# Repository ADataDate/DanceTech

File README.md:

# Dance and Cheer Tech

Creative computing kits for dancers and cheerleaders

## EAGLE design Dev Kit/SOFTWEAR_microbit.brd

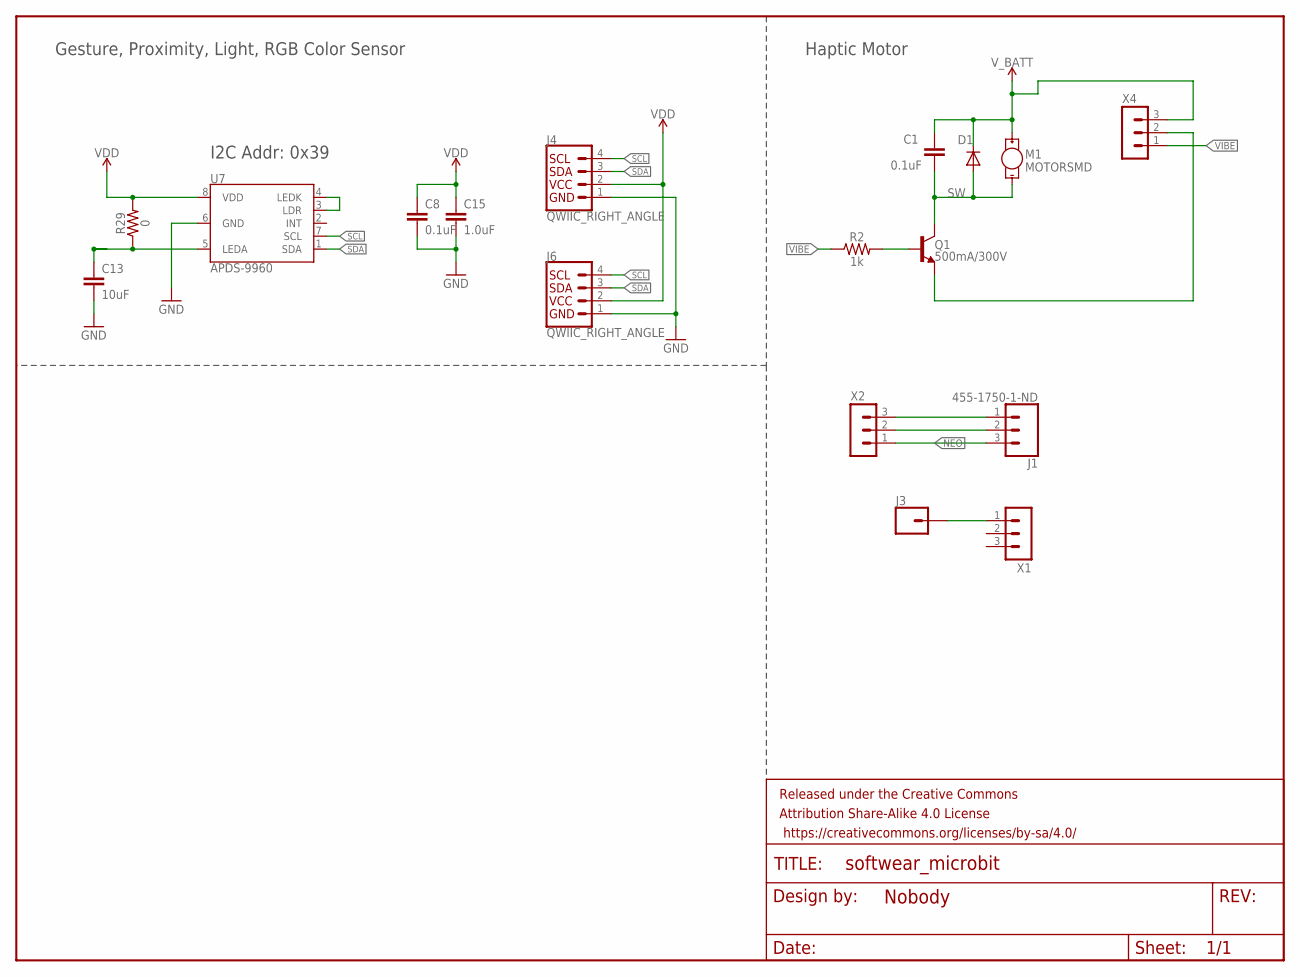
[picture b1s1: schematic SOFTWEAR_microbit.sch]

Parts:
C1, C8: 0.1uF; 0603
C13: 10uF; 0805
C15: 1.0uF; 0603
D1: DIODESOD; SOD-323
FRAME2: FRAME-LETTERNO_PACKAGE; DUMMY
J1: 455-1750-1-ND; 1X03
J3: CONN_01SPRING-CONN; SPRING-CONNECTOR
J4, J6: QWIIC_RIGHT_ANGLE; JST04_1MM_RA
M1: MOTORSMD; VIBE-MOTOR-10MM-SMD
Q1: 500mA/300V; SOT23-3
R2: 1k; 0603
R29: 0; 0603
U7: APDS-9960
X1, X2, X4: SM03B-SRSS-TB

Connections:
GND: C8.2, C13.2, C15.2, J4.1, J6.1, U7.6 (GND)
LEDA: C13.1, R29.1, U7.5 (LEDA)
unnamed: Q1.1 (B), R2.2
unnamed: J1.2, X2.2
unnamed: U7.3 (LDR), U7.4 (LEDK)
unnamed: J3.P$2, X1.1
unnamed: J1.1, X2.3
unnamed: Q1.2 (E), X4.2
NEO: J1.3, X2.1
SCL: J4.4, J6.4, U7.7 (SCL)
SDA: J4.3, J6.3, U7.1 (SDA)
SW: C1.2, D1.2 (A), M1.P$2 (-), Q1.3 (C)
VDD: C8.1, C15.1, J4.2, J6.2, R29.2, U7.8 (VDD)
VIBE: R2.1, X4.1
V_BATT: C1.1, D1.1 (C), M1.P$1 (+), X4.3

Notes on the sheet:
Haptic Motor
I2C Addr: 0x39
Gesture, Proximity, Light, RGB Color Sensor

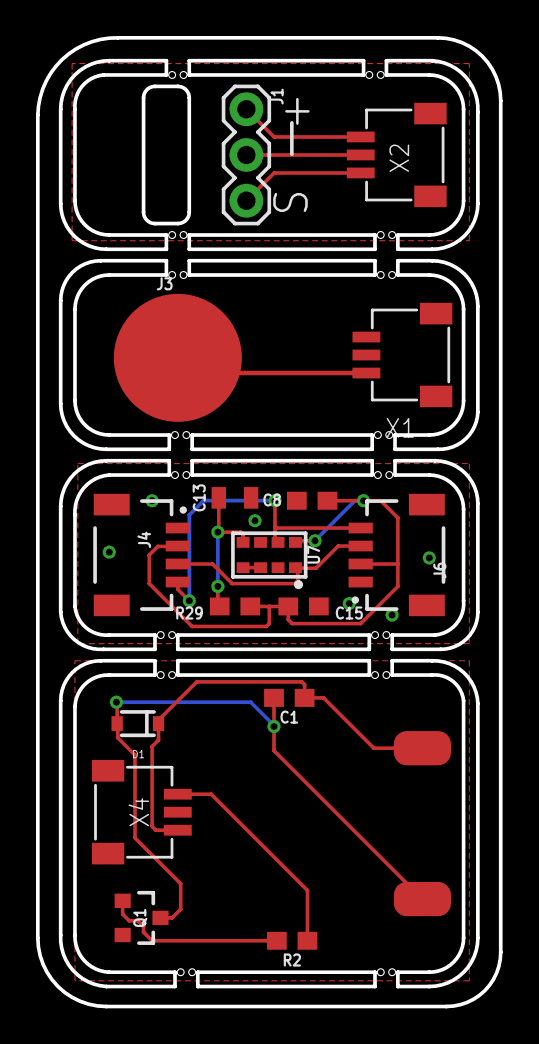
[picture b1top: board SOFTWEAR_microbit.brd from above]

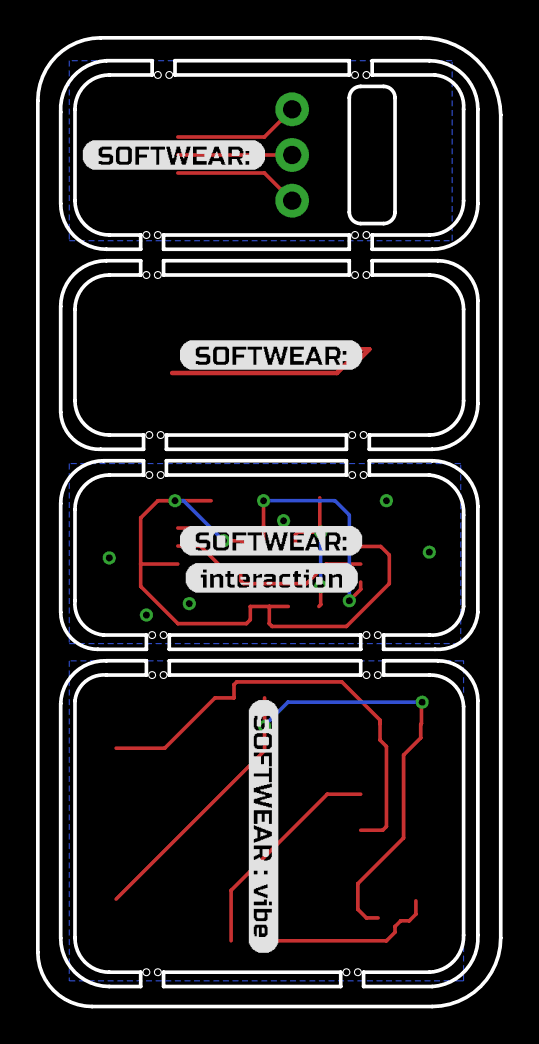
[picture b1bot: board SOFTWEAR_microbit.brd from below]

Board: 2 copper layers, 25.7 x 53.8 mm, 23 parts (5 on the bottom side), 15 nets.

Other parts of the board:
U$1, U$4, U$6: SOFTWEAR#3
U$2: INTERACTION1
U$5: SOFTWEAR_#_VIBE6

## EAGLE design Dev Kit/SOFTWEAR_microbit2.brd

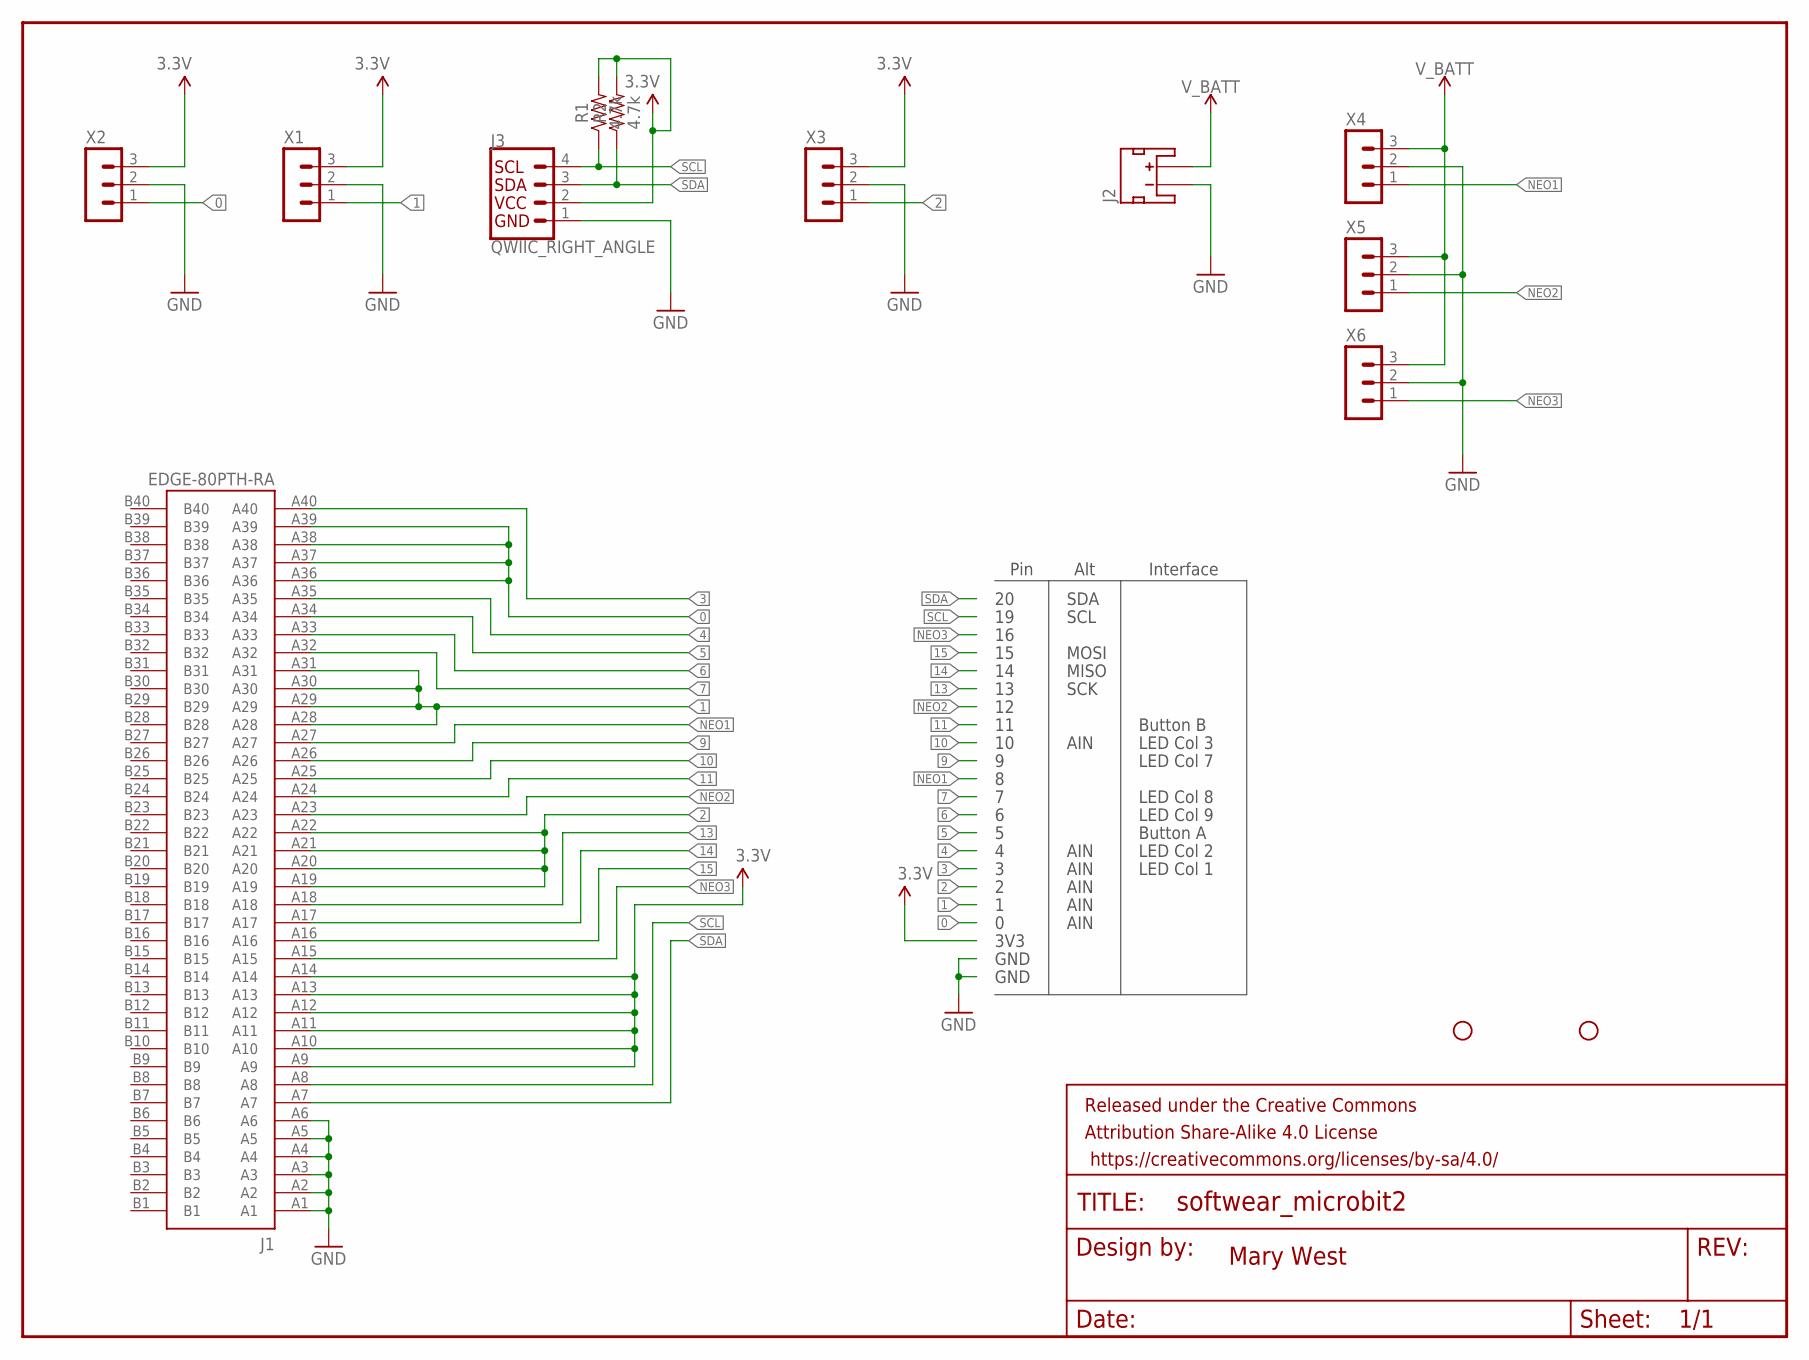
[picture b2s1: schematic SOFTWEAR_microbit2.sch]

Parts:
FRAME2: FRAME-LETTERNO_PACKAGE; DUMMY
H1, H2: STAND-OFF
J1: EDGE-80PTH-RA; VEC-127-080-R
J2: JST_2MM_MALE; JST-2-SMD
J3: QWIIC_RIGHT_ANGLE; JST04_1MM_RA
R1, R2: 4.7k; 0603
X1, X2, X3, X4, X5, X6: SM03B-SRSS-TB

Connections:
0: J1.A36, J1.A37, J1.A38, J1.A39, X2.1
1: J1.A28, J1.A29, J1.A30, J1.A31, X1.1
2: J1.A19, J1.A20, J1.A21, J1.A22, X3.1
3: J1.A40
3.3V: J1.A9, J1.A10, J1.A11, J1.A12, J1.A13, J1.A14, J3.2, R1.2, R2.2, X1.3, X2.3, X3.3
4: J1.A35
5: J1.A34
6: J1.A33
7: J1.A32
9: J1.A26
10: J1.A25
11: J1.A24
13: J1.A18
14: J1.A17
15: J1.A16
GND: J1.A1, J1.A2, J1.A3, J1.A4, J1.A5, J1.A6, J2.1 (-), J3.1, X1.2, X2.2, X3.2, X4.2, X5.2, X6.2
NEO1: J1.A27, X4.1
NEO2: J1.A23, X5.1
NEO3: J1.A15, X6.1
SCL: J1.A8, J3.4, R1.1
SDA: J1.A7, J3.3, R2.1
V_BATT: J2.2 (+), X4.3, X5.3, X6.3

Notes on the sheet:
GND
3V3
SCL
SDA
SCK
MISO
MOSI
AIN
Button B
LED Col 3
LED Col 7
LED Col 8
LED Col 9
LED Col 2
Button A
LED Col 1
Pin
Alt
Interface
Mary West

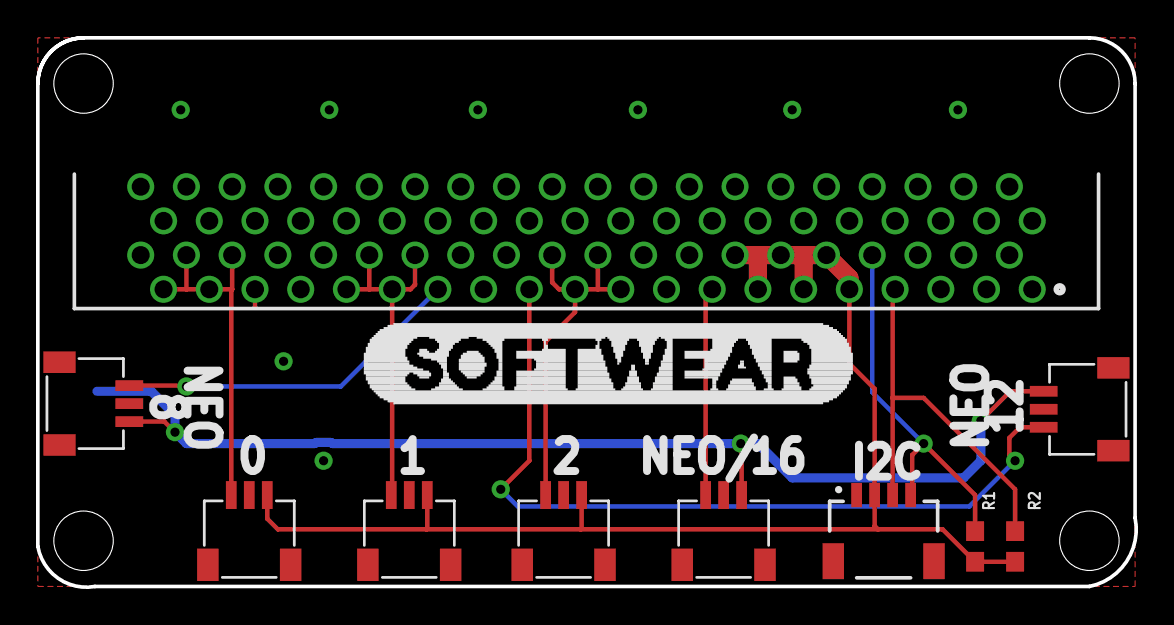
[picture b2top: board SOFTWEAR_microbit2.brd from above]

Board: 2 copper layers, 61.0 x 30.5 mm, 17 parts (1 on the bottom side), 11 nets.

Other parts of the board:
H3, H4: STAND-OFF
U$1: SOFTWEAR0

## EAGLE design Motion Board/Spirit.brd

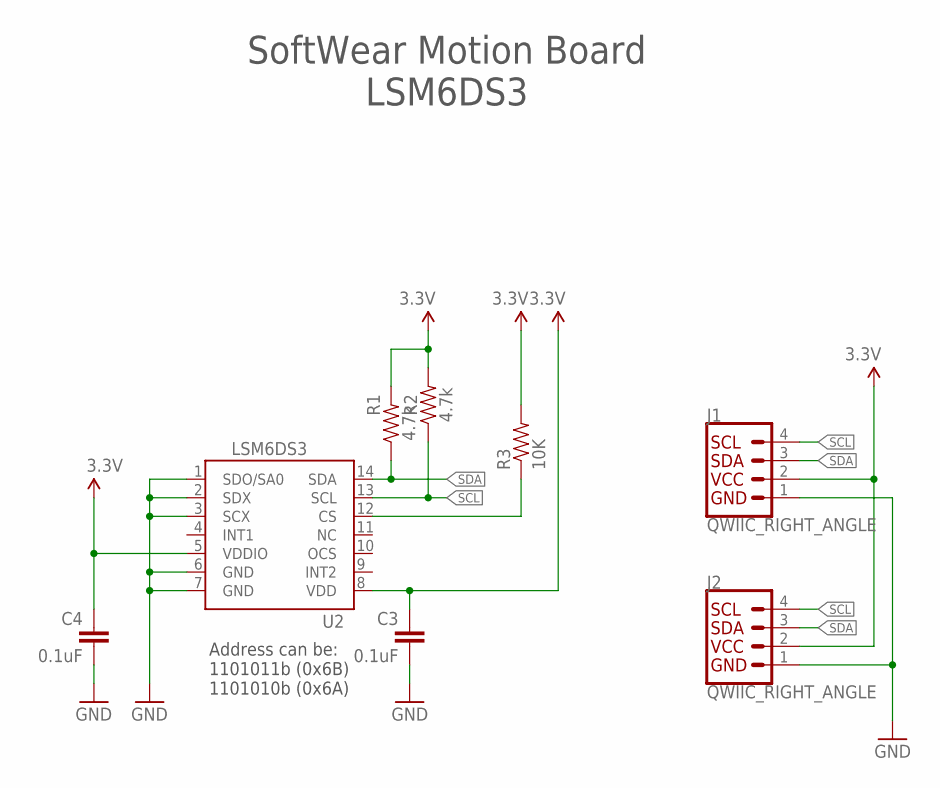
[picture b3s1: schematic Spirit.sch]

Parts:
C3, C4: 0.1uF; 0603-CAP
J1, J2: QWIIC_RIGHT_ANGLE; JST04_1MM_RA
R1, R2: 4.7k; 0603
R3: 10K; 0603-RES
U2: LSM6DS3; LGA14L_DOT_INDICATOR

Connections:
3.3V: C3.1, C4.1, J1.2, J2.2, R1.2, R2.2, R3.2, U2.5 (VDDIO), U2.8 (VDD)
CS: R3.1, U2.12 (CS)
GND: C3.2, C4.2, J1.1, J2.1, U2.1 (SDO/SA0), U2.2 (SDX), U2.3 (SCX), U2.6 (GND), U2.7 (GND)
SCL: J1.4, J2.4, R2.1, U2.13 (SCL)
SDA: J1.3, J2.3, R1.1, U2.14 (SDA)

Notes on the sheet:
SoftWear Motion Board LSM6DS3
Address can be: 1101011b (0x6B) 1101010b (0x6A)

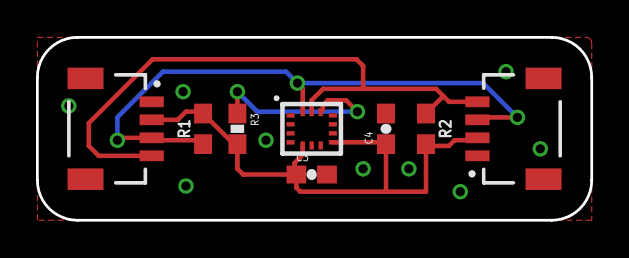
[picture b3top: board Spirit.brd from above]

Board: 2 copper layers, 30.8 x 10.2 mm, 8 parts (0 on the bottom side), 5 nets.

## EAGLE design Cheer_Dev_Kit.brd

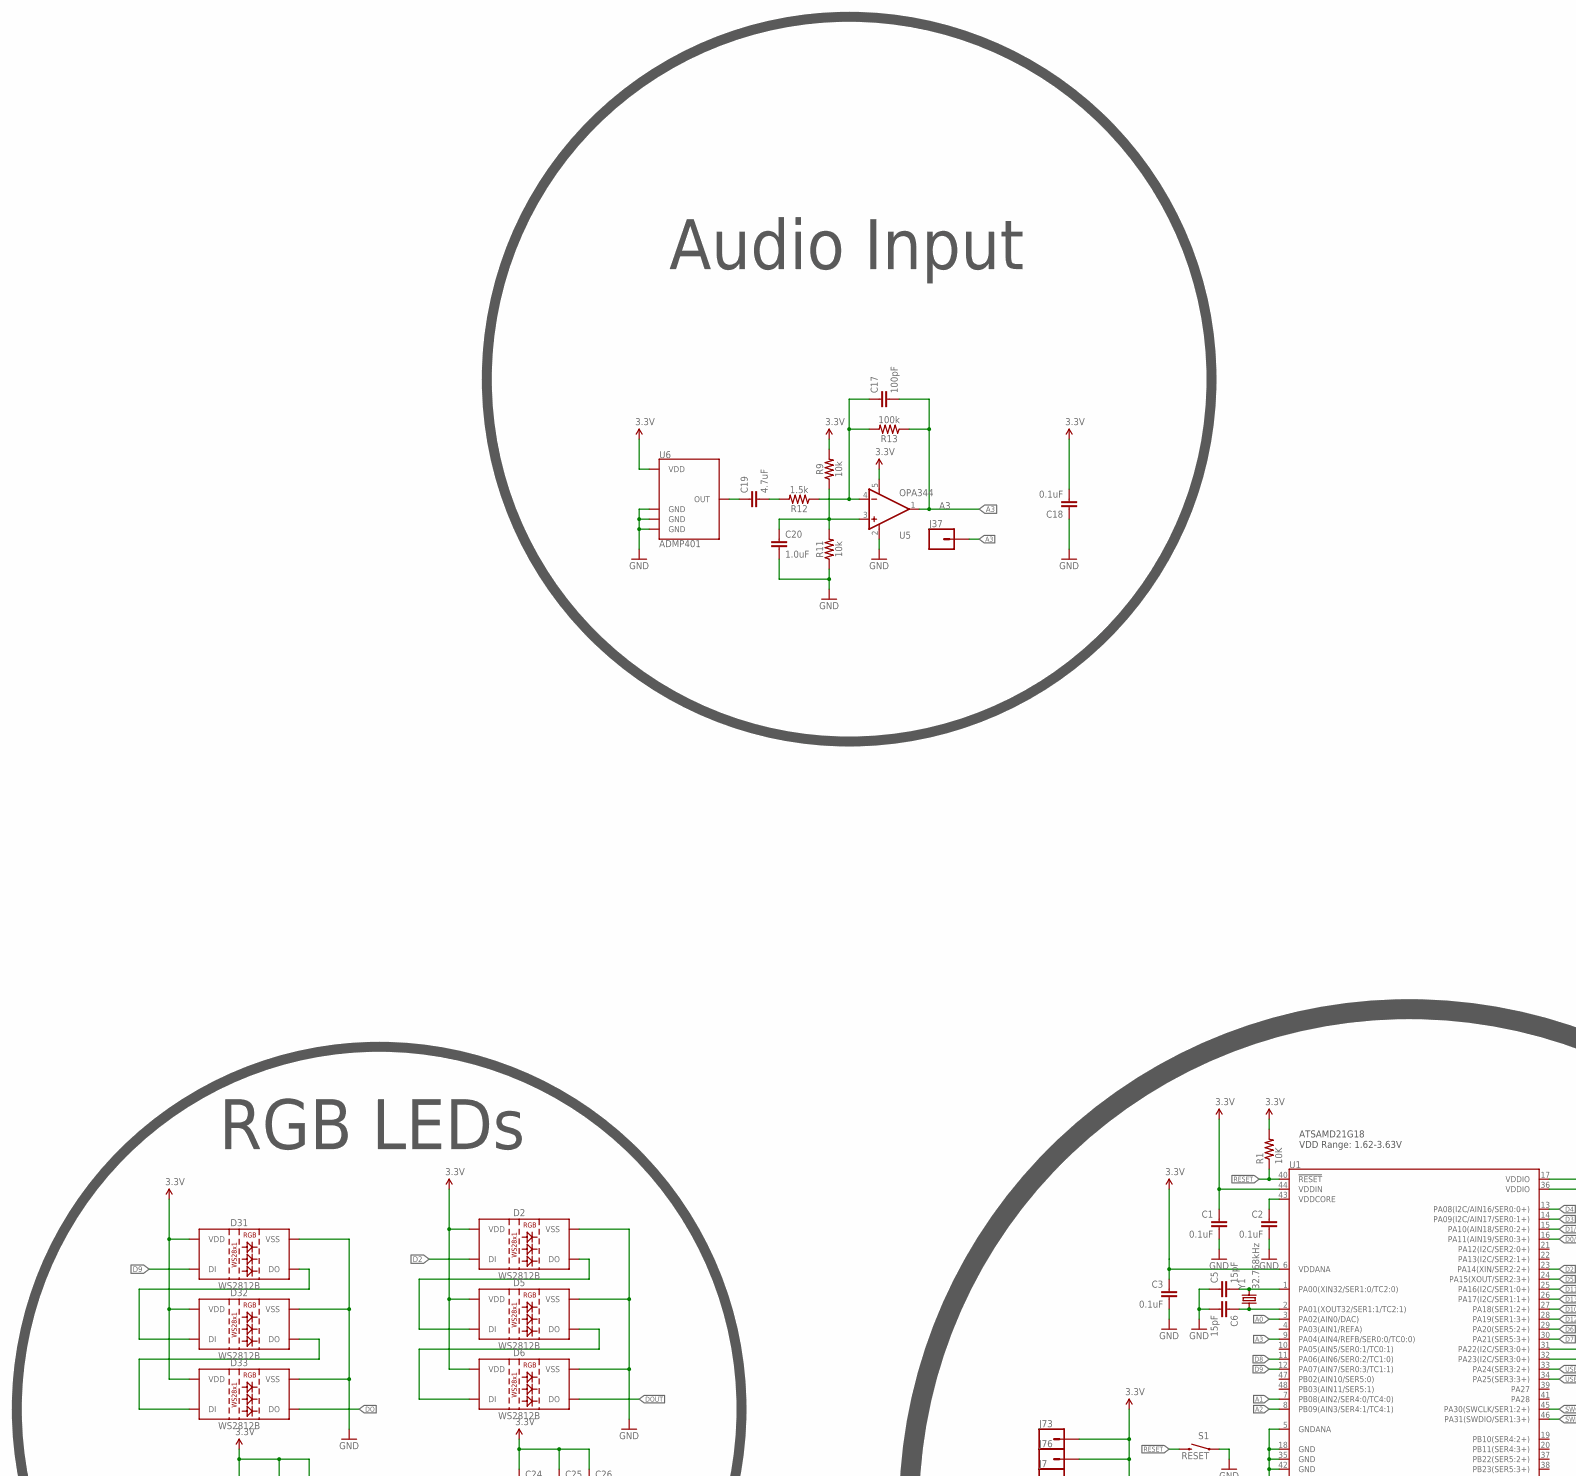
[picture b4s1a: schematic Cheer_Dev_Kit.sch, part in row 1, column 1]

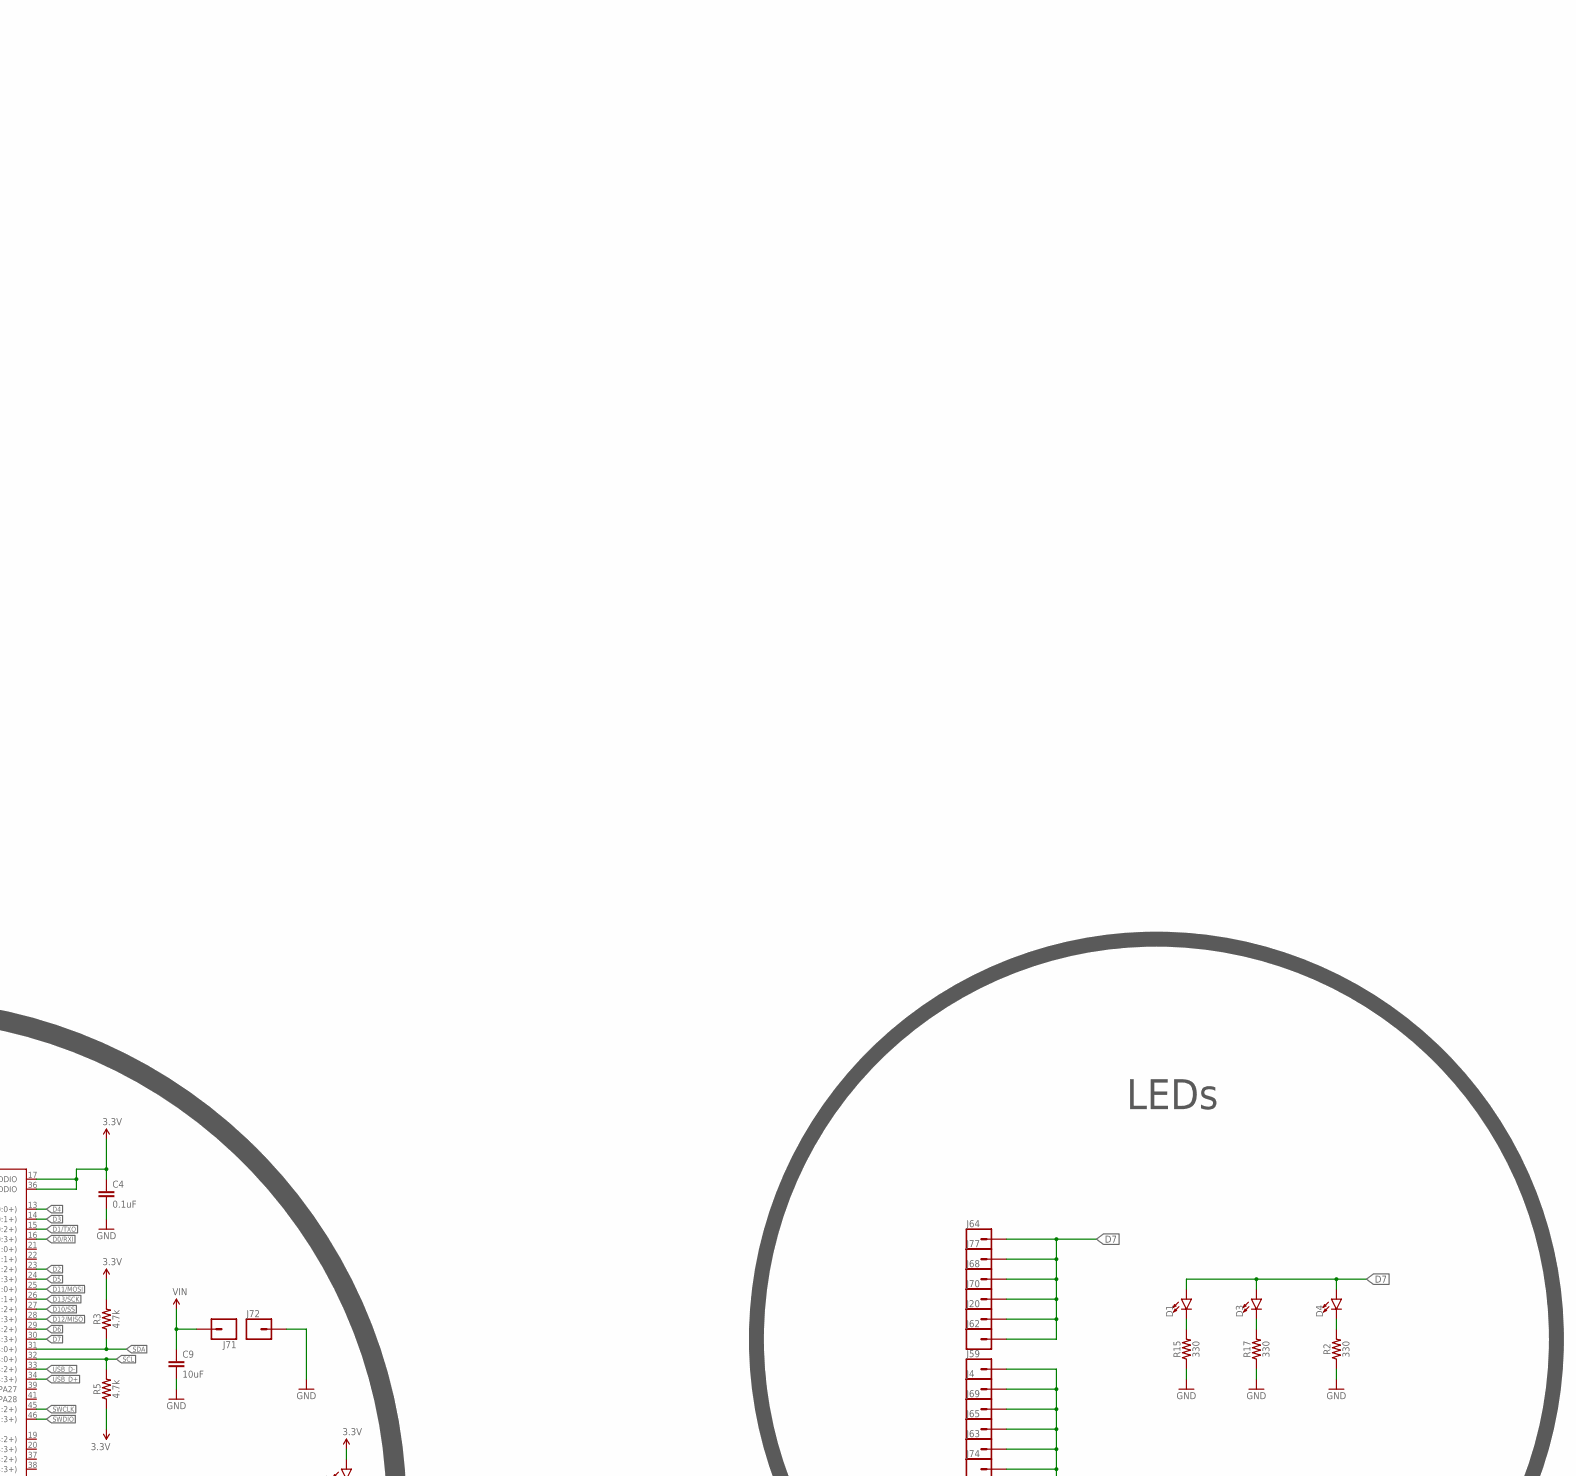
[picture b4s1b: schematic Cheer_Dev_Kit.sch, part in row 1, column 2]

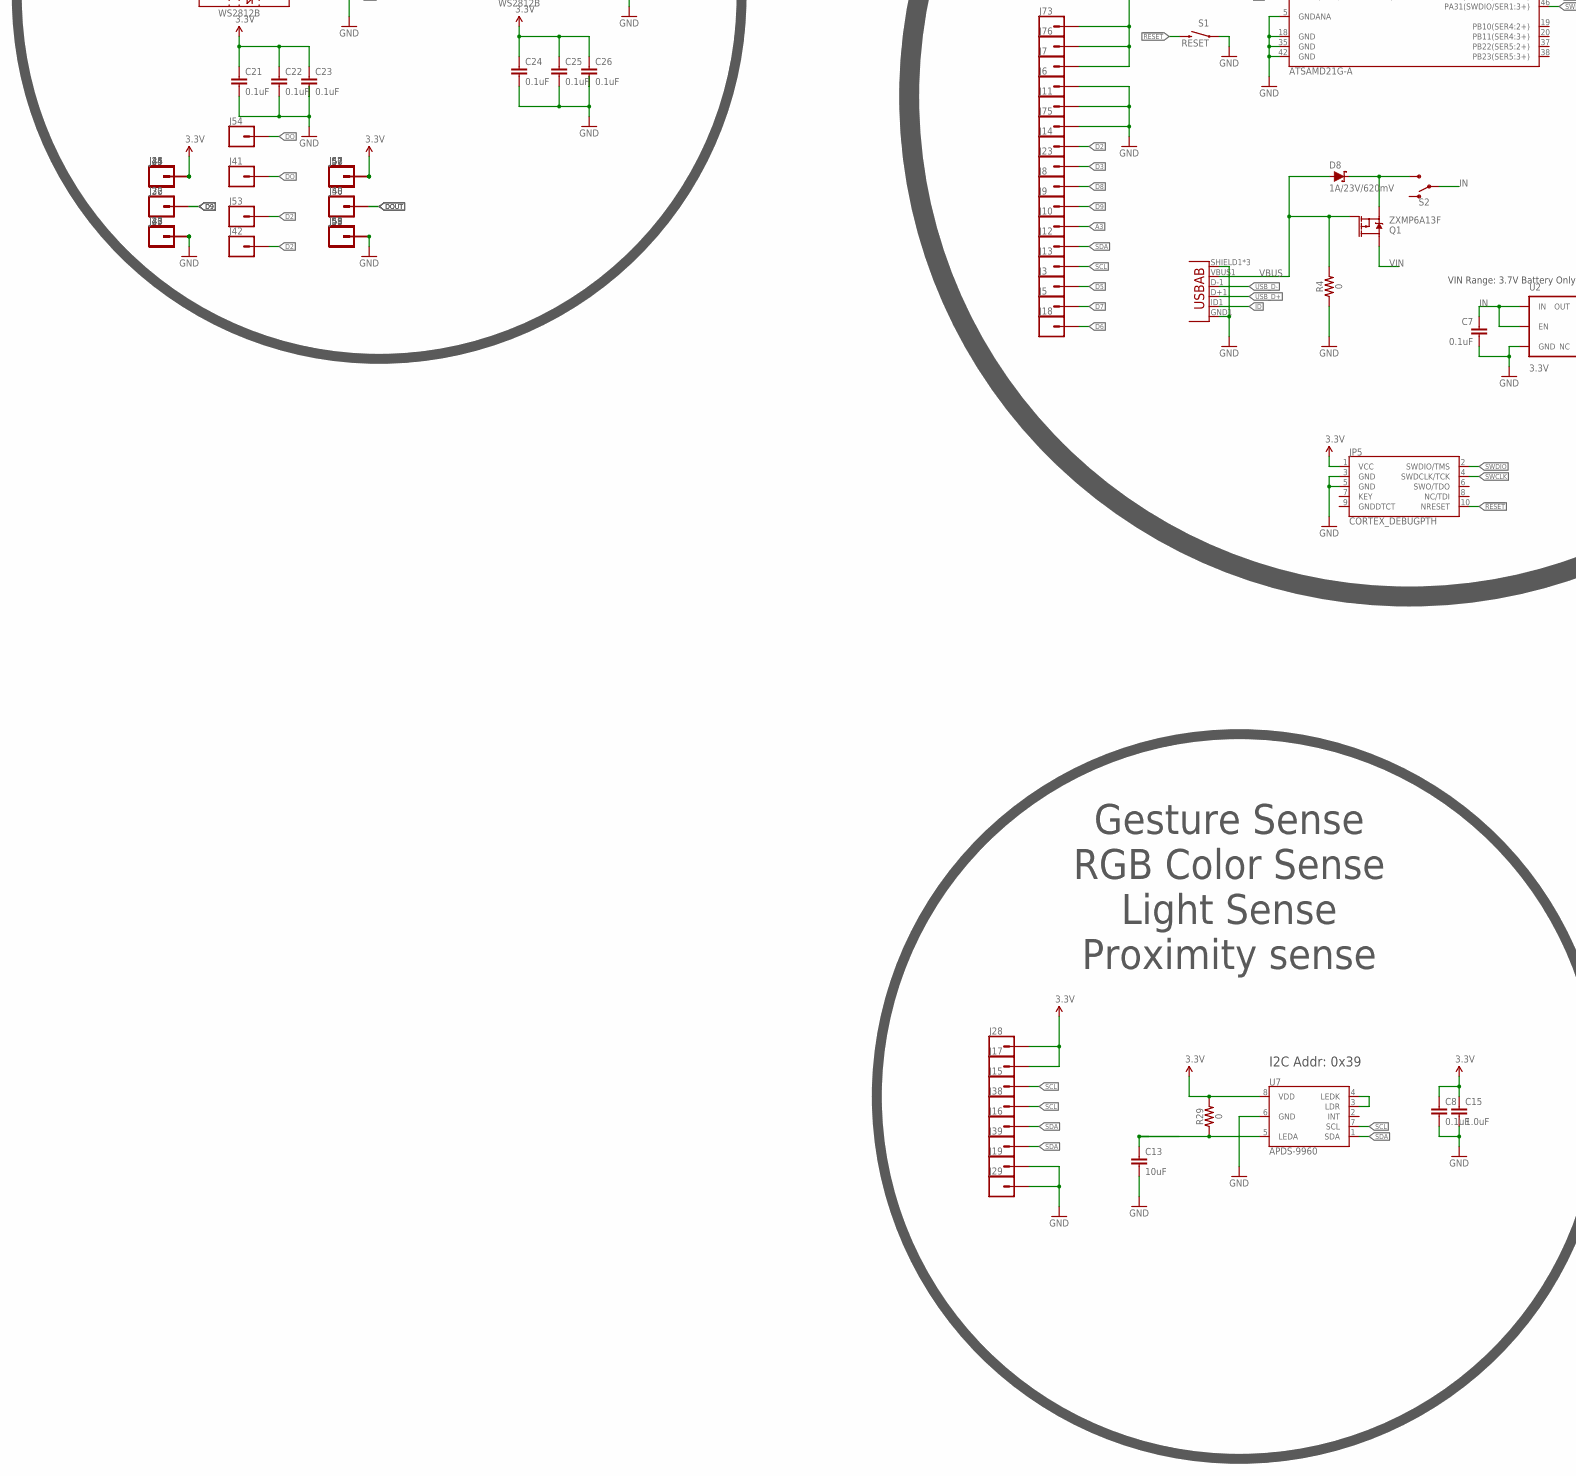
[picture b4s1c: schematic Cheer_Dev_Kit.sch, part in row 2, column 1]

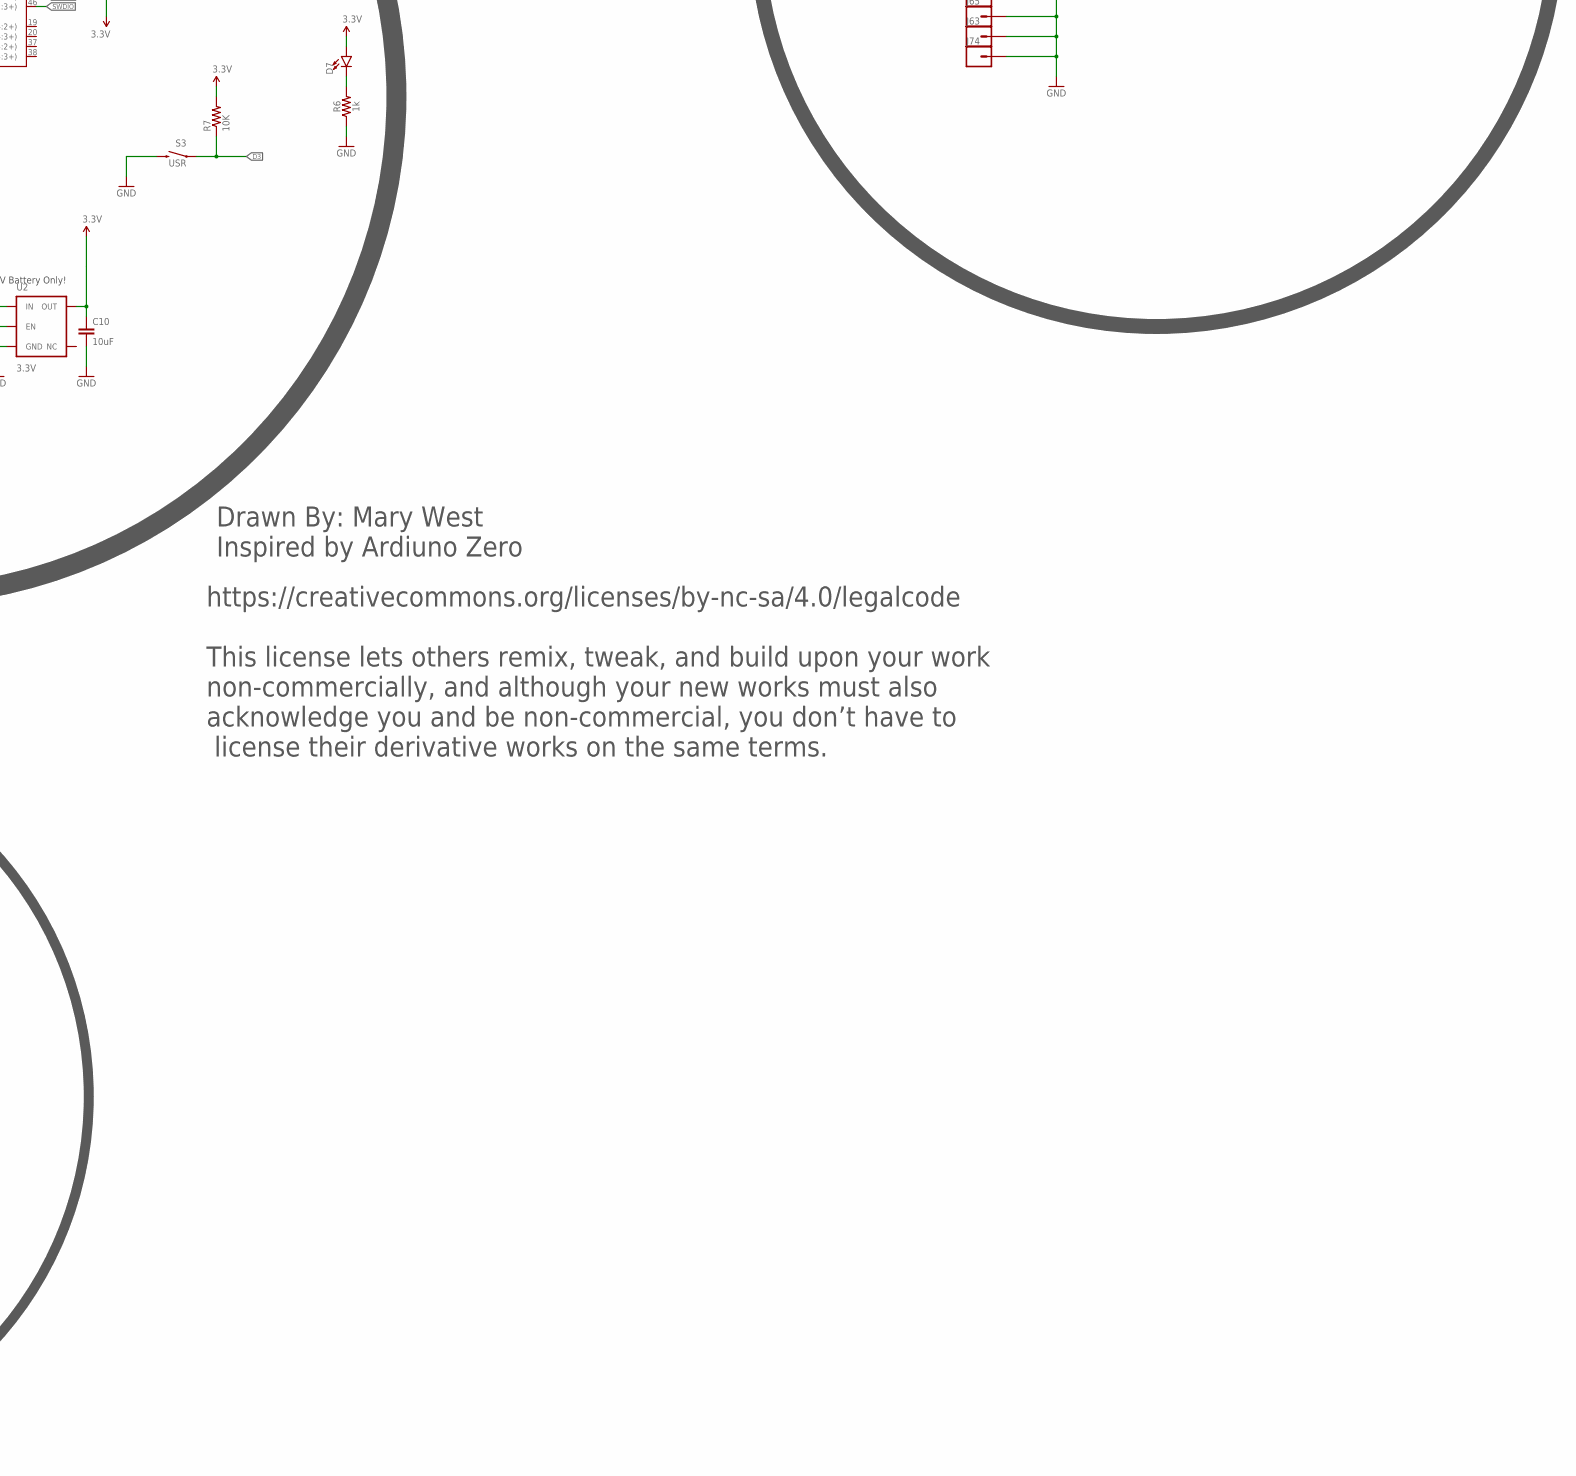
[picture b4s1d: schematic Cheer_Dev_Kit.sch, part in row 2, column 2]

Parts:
C1, C2, C3, C4, C7, C8, C18, C21, C22, C23, C24, C25, C26: 0.1uF; 0603
C5, C6: 15pF; 0603
C9, C10: 10uF; 0603
C13: 10uF; 0805
C15, C20: 1.0uF; 0603
C17: 100pF; 0603
C19: 4.7uF; 0603
D1, D3, D4, D7: LED1206; LED-1206
D2, D5, D6, D31, D32, D33: WS2812B
D8: 1A/23V/620mV; SOD-323
J3, J4, J5, J6, J7, J8, J9, J10, J11, J12, J13, J14, J15, J16, J17, J18, J19, J20, J23, J25, J26, J27, J28, J29, J32, J33, J34, J37, J38, J39, J41, J42, J43, J44, J45, J46, J47, J48, J49, J50, J51, J52, J53, J54, J55, J56, J57, J58, J59, J62, J63, J64, J65, J68, J69, J70, J71, J72, J73, J74, J75, J76, J77: CONN_01; 1X01
JP3: USB-ABCONN-11794; USB-AB-MICRO-SMD_V03
JP5: CORTEX_DEBUGPTH; 2X5-PTH-1.27MM
Q1: ZXMP6A13F; SOT23-3
R1, R7: 10K; 0603-RES@1
R2, R15, R17: 330; 0603
R3, R5: 4.7k; 0603
R4, R29: 0; 0603
R6: 1k; 0603
R9, R11: 10k; 0603
R12: 1.5k; 0603
R13: 100k; 0603
S1: RESET; TACTILE_SWITCH_SMD_4.6X2.8MM
S2: SWITCH-SPDT-SMD-AYZ0202; SWITCH_DPDT_SMD_AYZ0202
S3: USR; TACTILE_SWITCH_SMD_4.6X2.8MM
U1: ATSAMD21G-A; TQFP-48
U2: 3.3V; SOT23-5
U5: OPA344; SOT23-5
U6: ADMP401
U7: APDS-9960
Y1: 32.768kHz; CRYSTAL-SMD-3.2X1.5MM

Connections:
3.3V: C1.1, C3.1, C4.1, C8.1, C10.1, C15.1, C18.2, C21.1, C22.1, C23.1, C24.1, C25.1, C26.1, D2.1 (VDD), D5.1 (VDD), D6.1 (VDD), D7.A, D31.1 (VDD), D32.1 (VDD), D33.1 (VDD), J7.P$1, J17.P$1, J25.P$1, J28.P$1, J34.P$1, J44.P$1, J45.P$1, J47.P$1, J52.P$1, J56.P$1, J57.P$1, J73.P$1, J76.P$1, JP5.1 (VCC), R1.2, R3.2, R5.1, R7.2, R9.2, R29.2, U1.6 (VDDANA), U1.17 (VDDIO), U1.36 (VDDIO), U1.44 (VDDIN), U2.5 (OUT), U5.5 (V+), U6.5 (VDD), U7.8 (VDD)
!RESET: JP5.10 (NRESET), R1.1, S1.3 (2), S1.4 (2), U1.40 (!RESET!)
A0: U1.3 (PA02(AIN0/DAC))
A1: U1.7 (PB08(AIN2/SER4:0/TC4:0))
A2: U1.8 (PB09(AIN3/SER4:1/TC4:1))
A3: C17.2, J10.P$1, J37.P$1, R13.1, U1.9 (PA04(AIN4/REFB/SER0:0/TC0:0)), U5.1 (OUT)
D0/RXI: U1.16 (PA11(AIN19/SER0:3+))
D1/TXO: U1.15 (PA10(AIN18/SER0:2+))
D2: D2.4 (DI), J14.P$1, J42.P$1, J53.P$1, U1.23 (PA14(XIN/SER2:2+))
D3: J23.P$1, R7.1, S3.1, S3.2 (1), U1.14 (PA09(I2C/AIN17/SER0:1+))
D4: U1.13 (PA08(I2C/AIN16/SER0:0+))
D5: J3.P$1, U1.24 (PA15(XOUT/SER2:3+))
D6: J18.P$1, U1.29 (PA20(SER5:2+))
D7: D1.A, D3.A, D4.A, J5.P$1, J20.P$1, J62.P$1, J64.P$1, J68.P$1, J70.P$1, J77.P$1, U1.30 (PA21(SER5:3+))
D8: J8.P$1, U1.11 (PA06(AIN6/SER0:2/TC1:0))
D9: D31.4 (DI), J9.P$1, J26.P$1, J32.P$1, U1.12 (PA07(AIN7/SER0:3/TC1:1))
D10/SS: U1.27 (PA18(SER1:2+))
D11/MOSI: U1.25 (PA16(I2C/SER1:0+))
D12/MISO: U1.28 (PA19(SER1:3+))
D13/SCK: U1.26 (PA17(I2C/SER1:1+))
DO: D33.2 (DO), J41.P$1, J54.P$1
DOUT: D6.2 (DO), J48.P$1, J50.P$1
GND: C1.2, C2.2, C3.2, C4.2, C5.1, C6.2, C7.2, C8.2, C9.2, C10.2, C13.2, C15.2, C18.1, C20.2, C21.2, C22.2, C23.2, C24.2, C25.2, C26.2, D2.3 (VSS), D5.3 (VSS), D6.3 (VSS), D31.3 (VSS), D32.3 (VSS), D33.3 (VSS), J4.P$1, J6.P$1, J11.P$1, J19.P$1, J27.P$1, J29.P$1, J33.P$1, J43.P$1, J46.P$1, J49.P$1, J51.P$1, J55.P$1, J58.P$1, J59.P$1, J63.P$1, J65.P$1, J69.P$1, J72.P$1, J74.P$1, J75.P$1, JP3.GND1 (GND), JP3.SHIELD1 (SHIELD), JP3.SHIELD2 (SHIELD), JP3.SHIELD3 (SHIELD), JP5.3 (GND), JP5.5 (GND), R2.1, R4.1, R6.1, R11.1, R15.1, R17.1, S1.1, S1.2 (1), S3.3 (2), S3.4 (2), U1.5 (GNDANA), U1.18 (GND), U1.35 (GND), U1.42 (GND), U2.2 (GND), U5.2 (V-), U6.2 (GND), U6.4 (GND), U6.6 (GND), U7.6 (GND)
ID: JP3.ID1 (USBID)
IN: C7.1, S2.2, U2.1 (IN), U2.3 (EN)
LEDA: C13.1, R29.1, U7.5 (LEDA)
unnamed: D4.C, R2.2
unnamed: C5.2, U1.1 (PA00(XIN32/SER1:0/TC2:0)), Y1.P$2 (2)
unnamed: C19.1, U6.1 (OUT)
unnamed: C6.1, U1.2 (PA01(XOUT32/SER1:1/TC2:1)), Y1.P$1 (1)
unnamed: U7.3 (LDR), U7.4 (LEDK)
unnamed: C17.1, R12.1, R13.2, U5.4 (-IN)
unnamed: D7.C, R6.2
unnamed: D8.C, Q1.2 (S), S2.3 (S)
unnamed: C19.2, R12.2
unnamed: C20.1, R9.1, R11.2, U5.3 (+IN)
unnamed: D1.C, R15.2
unnamed: D31.2 (DO), D32.4 (DI)
unnamed: D3.C, R17.2
unnamed: D32.2 (DO), D33.4 (DI)
unnamed: D2.2 (DO), D5.4 (DI)
unnamed: D5.2 (DO), D6.4 (DI)
SCL: J13.P$1, J15.P$1, J38.P$1, R5.2, U1.32 (PA23(I2C/SER3:0+)), U7.7 (SCL)
SDA: J12.P$1, J16.P$1, J39.P$1, R3.1, U1.31 (PA22(I2C/SER3:0+)), U7.1 (SDA)
SWCLK: JP5.4 (SWDCLK/TCK), U1.45 (PA30(SWCLK/SER1:2+))
SWDIO: JP5.2 (SWDIO/TMS), U1.46 (PA31(SWDIO/SER1:3+))
USB_D+: JP3.D+1 (D+), U1.34 (PA25(SER3:3+))
USB_D-: JP3.D-1 (D-), U1.33 (PA24(SER3:2+))
VBUS: D8.A, JP3.VBUS1 (VBUS), Q1.1 (G), R4.2
VDDCORE: C2.1, U1.43 (VDDCORE)
VIN: C9.1, J71.P$1, Q1.3 (D)

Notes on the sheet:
ATSAMD21G18 VDD Range: 1.62-3.63V
VIN Range: 3.7V Battery Only!
LEDs
Audio Input
Gesture Sense RGB Color Sense Light Sense Proximity sense
I2C Addr: 0x39
RGB LEDs
https://creativecommons.org/licenses/by-nc-sa/4.0/legalcode This license lets others remix, tweak, and build upon your work non-commercially, and although your new works must also acknowledge you and be non-commercial, you don’t have to license their derivative works on the same terms.
Drawn By: Mary West Inspired by Ardiuno Zero

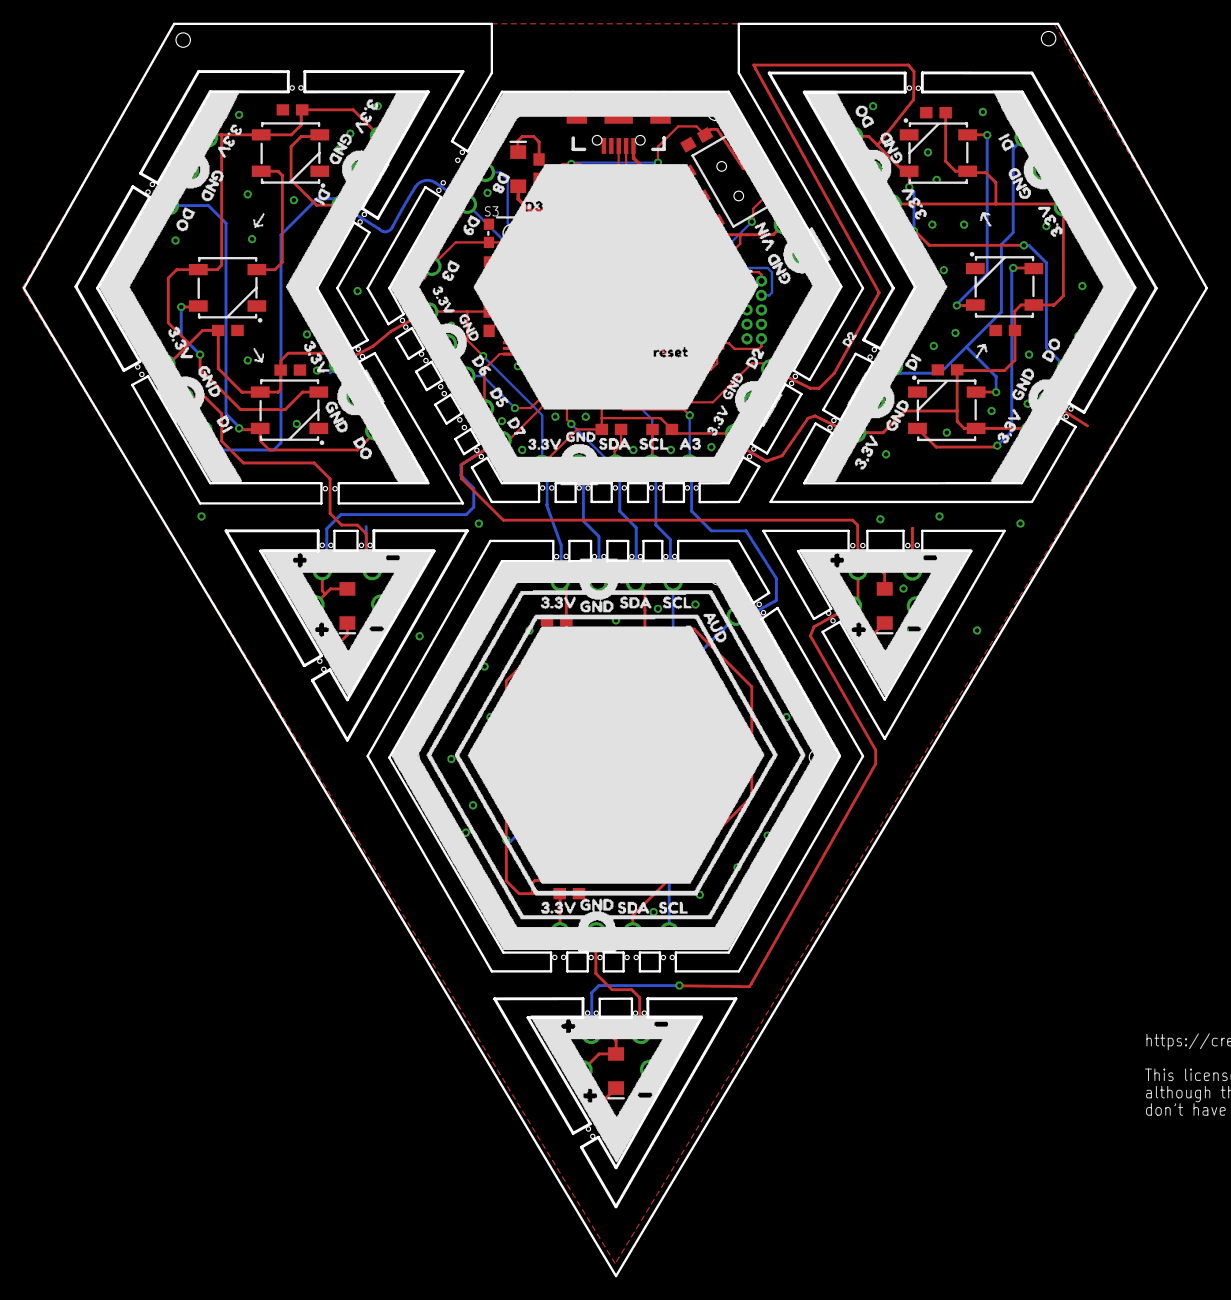
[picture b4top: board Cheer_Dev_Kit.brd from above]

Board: 2 copper layers, 104.0 x 110.1 mm, 124 parts (0 on the bottom side), 40 nets.

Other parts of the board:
U$2: HACKMODWEAR_V2SILK_DRAFT_BUZZARDTOP#01#JPG
U$3: HACKMODWEAR_V2SILK_DRAFT_BUZZARDBOTTOM#01#JPG

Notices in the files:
parts and their libraries:
SparkFun-Capacitors: Licensing: Creative Commons ShareAlike 4.0 International - https://creativecommons.org/licenses/by-sa/4.0
microbuilder: This work is placed in the public domain, and may be freely used for commercial and non-commercial work with the following conditions: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
